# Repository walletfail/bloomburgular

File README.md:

# Bloomburgular -- the super micro fun implant

## Goals of the implant

The design of the implant had the following constraints:

- Could occur during the supply chain OR after customer has taken
  receipt of the drive (think red team or insider threat)
- Requires zero firmware
- Fits inside the Nano S
- Bypasses a core security function
- Few components (cheap and DIY)
- FUN to build and use (not bluetooth)

## Theory of Operation

When the selected RF signal is detected, the output is pulled low.

That's it.

## Parts:

- C1: DC Blocking CAP
- R3: Pot for voltage adjustment (see notes below)
- Q1: NPN Transistor
- R1: Bias resistor
- R2 & C2: Low pass filter

## Operating Tips

The only thing tuning this circuit is the antenna. Experiment with
different antennas for different frequencies! We used 17cm for decent
reception at 433MHz. At 433Mhz, we had a 50W transmitter around so
that was fun :)

For the pot, you can make your circuit more or less sensitive. We
adjusted ours so that the output (GPIO) came down to about 2.9V. If
the pot is too low, you'll need a strong signal and too high, it will
pull the GPIO low without any RF.

## Improvements

You can remove the put and put in your own voltage divider and that
will save 80 percent of the BoM. Worse case, you will have to tune by
reworking SMD resistors, which isn't so bad.

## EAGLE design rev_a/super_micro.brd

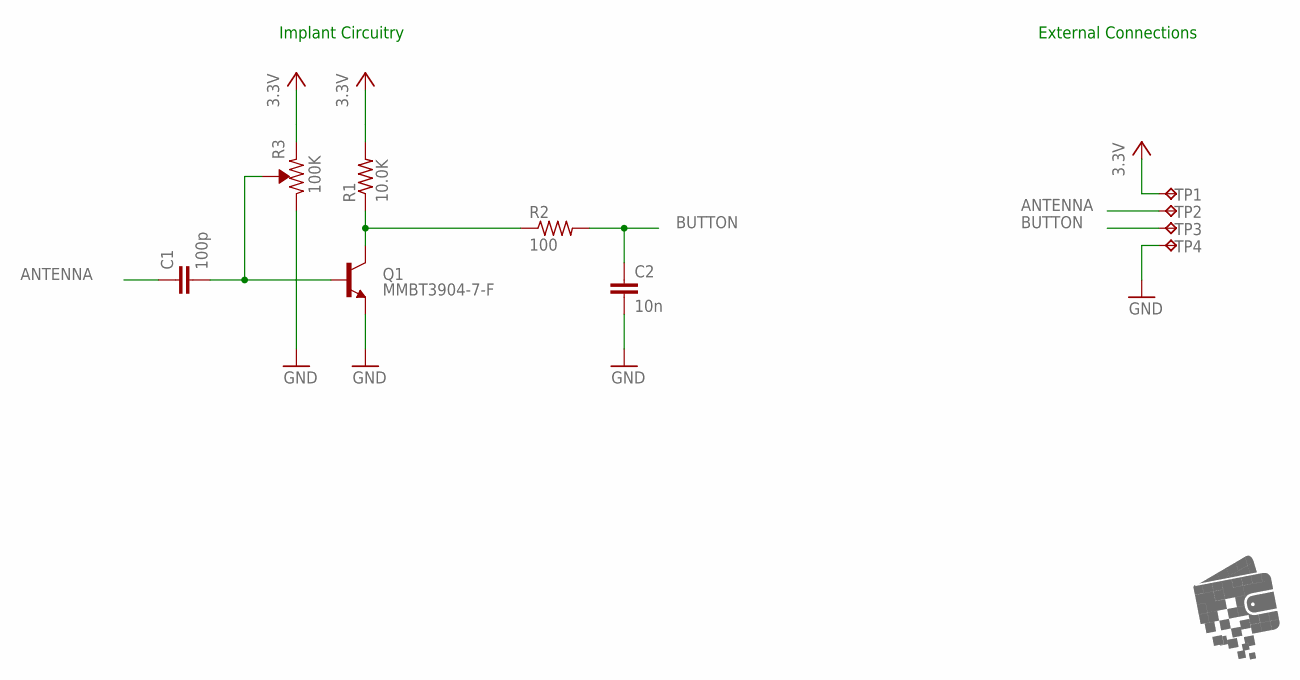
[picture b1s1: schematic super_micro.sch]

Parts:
C1: 100p; C0603
C2: 10n; C0603
LOGO1: WF_LOGO_S
Q1: MMBT3904-7-F; SOT-23
R1: 10.0K; R0603
R2: 100; R0603
R3: 100K; 3312J
TP1, TP2, TP3, TP4: TEST-POINT40MIL; TEST-POINT-40MILL

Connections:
0V: C2.2, Q1.2 (E), R3.1, TP4.1
3.3V: R1.2, R3.3, TP1.1
ANTENNA: C1.1, TP2.1
BUTTON: C2.1, R2.2, TP3.1
unnamed: Q1.3 (C), R1.1, R2.1
unnamed: C1.2, Q1.1 (B), R3.2

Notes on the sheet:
Implant Circuitry
External Connections

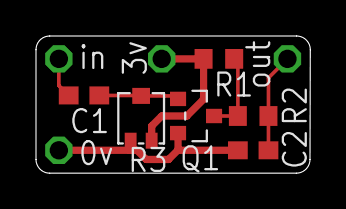
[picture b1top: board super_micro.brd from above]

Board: 2 copper layers, 15.2 x 7.6 mm, 11 parts (1 on the bottom side), 6 nets.

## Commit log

2019-01-10 published.
